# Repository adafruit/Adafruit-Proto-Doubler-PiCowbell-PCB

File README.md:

## Adafruit Proto Doubler PiCowbell for Pico and PicoW PCB

<a href="http://www.adafruit.com/products/5906"><br/>
Click here to purchase one from the Adafruit shop</a>

PCB files for the Adafruit Proto Doubler PiCowbell for Pico and PicoW. 

Format is EagleCAD schematic and board layout
* https://www.adafruit.com/product/5906

### Description

The Adafruit Proto Doubler PiCowBell is intended to be treated like a mini solder-less proto plate to simplify programming and sensor connectivity for your Raspberry Pi Pico board. Reset button? Yes! STEMMA QT / Qwiic connector for fast I2C? Indeed. Battery with recharging and on/off switch? Affirmative. Plug-and-play so no soldering necessary when used with a Pico H or Pico WH? Here you go!

The Doubler is like if we used a 'Clone Tool' on the Proto Under Plate PiCowbell - you get two slots side-by-side which means you can easily add accessories to your Pico or Pico W without soldering on any stacking headers.

### LiPoly Battery Charging Support
The Doubler also gives you Lipoly/LiIon support circuitry so you can take your Pico project on the go. Use any 3.7V/4.2V single-cell Lithium battery with a JST 2-PH connector in the correct polarity. The battery will automagically charge with the Pico is plugged into USB, and switch over seamlessly to battery when USB power is removed.

By default the charge rate is 500mA for use with 500mAh+ sized batteries. You can cut a jumper to reduce the charge rate to 250mA if using 250mAh to 500mAh battery. So you don't have to unplug the battery often, a slide switch is connected to the Pico Enable pin, so you can disable the Pico's 3.3V power supply completely - this is as close as we can get to 'turning off' the Pico.

### Alkaline/NiMH Battery Pack Support
You can also cut a different jumper to disconnect the charger completely from the battery, which means you can use 3xAA or 3xAAA battery packs for alkaline or NiMH battery usage. Of course, you will need an external NiMH charger in that case. 

### Double Socket Headers
This board has double sockets already soldered on, you can plug in your Pico and 'Bell boards directly in, and get access to a prototyping area underneath as well as a second row of socket pins. The second row means you can connect wires just by poking them into the header, either directly to LEDs or buttons or to jumper to a breadboard. So you don't have to look up or count pins, each socket is nicely labeled. There's also 4 mounting holes for easy attachment to an underplate. 

The dual socket headers we use are 'hollow' - that means you can connect through the back if desired. Specifically, you can use Pico Stacking Headers to plug through to some other device that is expecting Pico pins. Also, in theory, if you soldered pin headers on the 'wrong side' of a Pico, you could plug it up through the bottom.

We recommend picking up a set of little rubber feet to protect your desk if you're not mounting this board to something else.

### Features:
* Two 2x20 slim socket headers - plug in your Pico and desired 'Bell and have an extra row of sockets for each pin!
* JST PH connector for LiIon/LiPoly or Alkaline/NiMH battery usage - be sure to cut the "disable charge" jumper to use Alkaline/NiMH batteries.
* LiPoly/LiIon charging circuitry for any 3.7V/4.2V nominal 1-cell battery. Default rate is 500mA, can be set to 250mA by cutting the charge-rate jumper on bottom. Two indicator LEDs let you know if battery is charging (orange) or complete (green)
* Slide switch connected to the Pico Enable pin, which will disable the 3.3V power supply.
* Reset button that sticks out the end
* JST SH connector for I2C / Stemma QT / Qwiic connection. Or can use it for plain GPIO wiring if you don't have any I2C devices to attach. Provides 3V, GND, IO4 (SDA), and IO5 (SCL)
* There is an extra set of 4 breakout holes next to the JST SH if you want more I2C connections or want to re-assign the I2C port.
* 3 hole-connected strips are in the center areas. You can cut the traces between the holes, but they're intended to be treated like a mini-mini breadboard
* Nearly-every pad on the Pico has a duplicate hole pad next to it for solder-jumpering
* The ground pads have white silkscreen rectangles to easily identify, plus one long ground strip near the reset button
* One long strip of connected holes for 3.3V power
* Gold-plated pads for easy soldering

We do not have I2C pullups on the board, but your Qwiic/QT breakout board or accessory likely already has them onboard. If using the Philhower Arduino core, the Wire peripheral is already set up to use IO4 and IO5. If using CircuitPython or MicroPython, you'll need to let the code know to look at 4+5 for SDA+SCL pins.

### License

Adafruit invests time and resources providing this open source design, please support Adafruit and open-source hardware by purchasing products from [Adafruit](https://www.adafruit.com)!

Designed by Limor Fried/Ladyada for Adafruit Industries.

Creative Commons Attribution/Share-Alike, all text above must be included in any redistribution. 
See license.txt for additional details.

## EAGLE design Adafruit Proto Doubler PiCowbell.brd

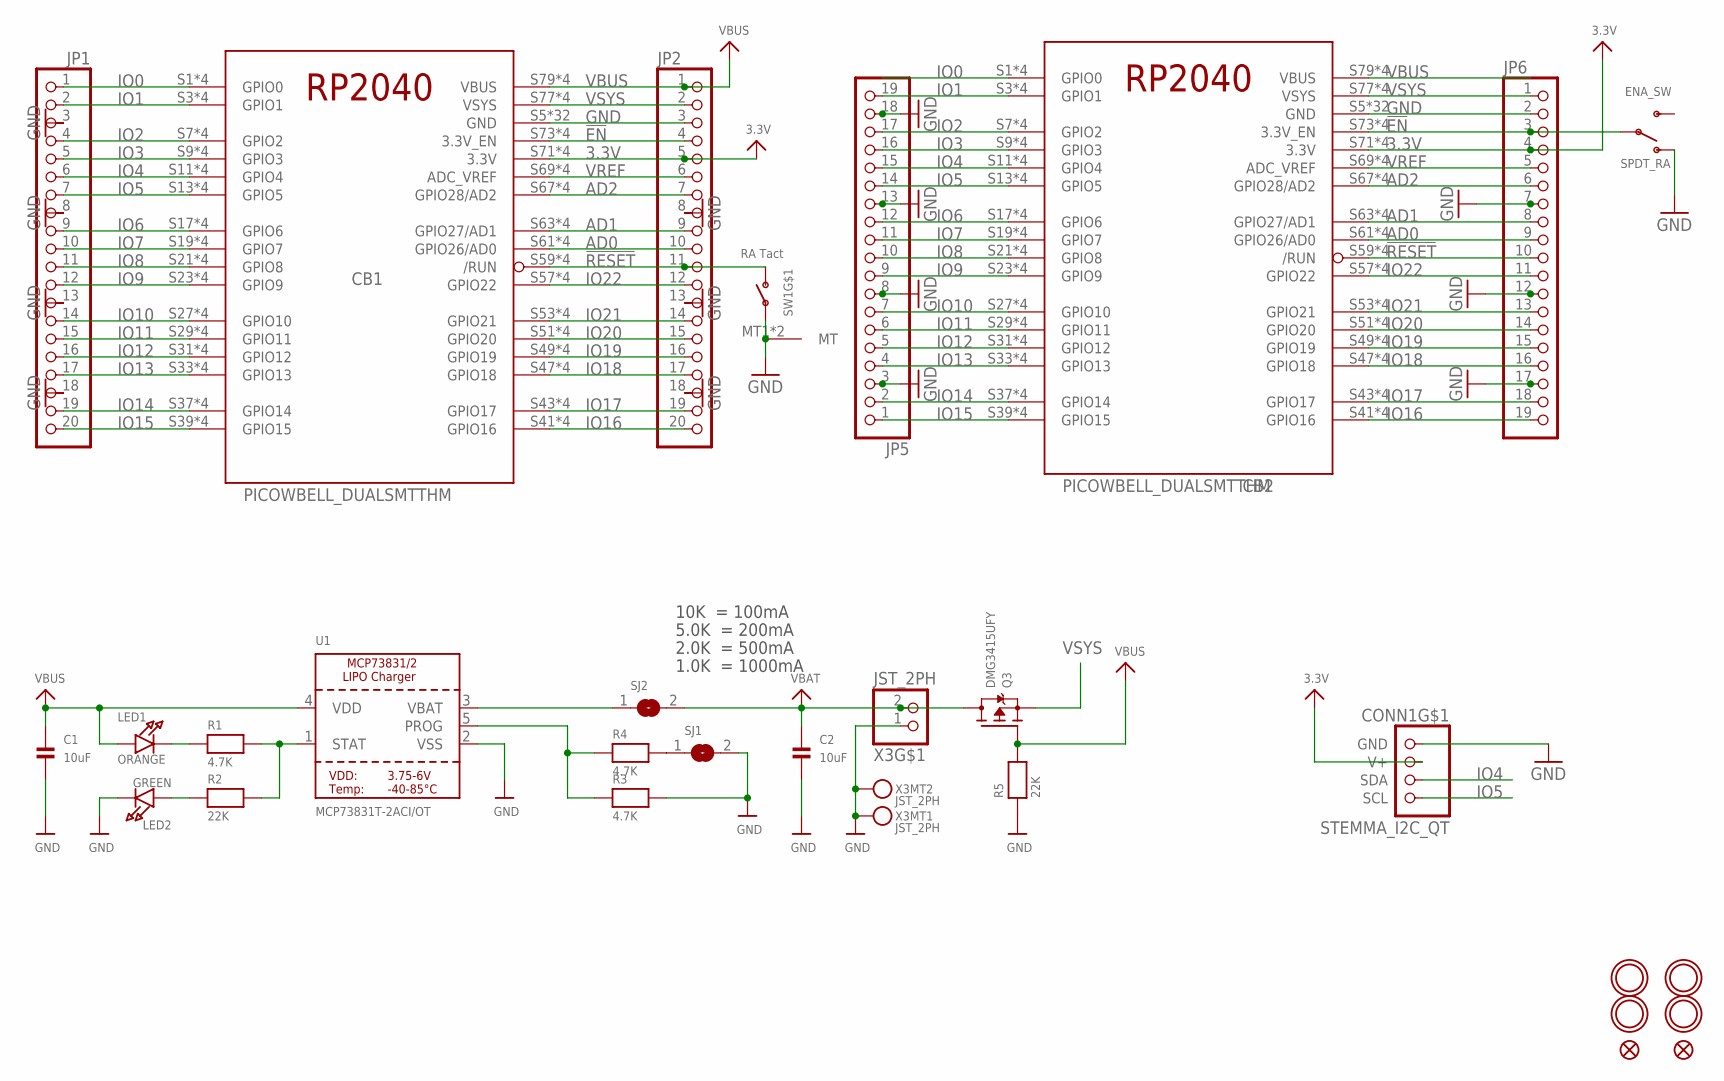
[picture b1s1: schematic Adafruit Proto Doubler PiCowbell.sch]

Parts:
C1, C2: 10uF; 0805-NO
CB1, CB2: PICOWBELL_DUALSMTTHM
CONN1: STEMMA_I2C_QT; JST_SH4
ENA_SW: SPDT_RA; SPDT_SMT_SSSS811101
FID1, FID2: FIDUCIAL_1MM
JP1, JP2: HEADER-1X20_70MIL; 1X20_ROUND_70MIL
JP5, JP6: HEADER-1X19; 1X19_ROUND
LED1: ORANGE; CHIPLED_0603_NOOUTLINE
LED2: GREEN; CHIPLED_0603_NOOUTLINE
Q3: DMG3415UFY; DFN2015-3
R1, R3, R4: 4.7K; _0402NO
R2, R5: 22K; _0402NO
SJ1, SJ2: SOLDERJUMPERCLOSED; SOLDERJUMPER_CLOSEDWIRE
SW1: RA Tact; SPST_TACTILE_RA
U1: MCP73831T-2ACI/OT; SOT23-5; JLC_ROTATION 0
U$5, U$7, U$15, U$16: MOUNTINGHOLE2.5; MOUNTINGHOLE_2.5_PLATED
X3: JST_2PH; JSTPH2_BATT

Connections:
3.3V: CB1.S71 (3.3V), CB1.S72 (3.3V), CB1.T71 (3.3V), CB1.T72 (3.3V), CB2.S71 (3.3V), CB2.S72 (3.3V), CB2.T71 (3.3V), CB2.T72 (3.3V), CONN1.2 (V+), JP2.5, JP6.4
!EN: CB1.S73 (3.3V_EN), CB1.S74 (3.3V_EN), CB1.T73 (3.3V_EN), CB1.T74 (3.3V_EN), CB2.S73 (3.3V_EN), CB2.S74 (3.3V_EN), CB2.T73 (3.3V_EN), CB2.T74 (3.3V_EN), ENA_SW.B, JP2.4, JP6.3
!RESET: CB1.S59 (/RUN), CB1.S60 (/RUN), CB1.T59 (/RUN), CB1.T60 (/RUN), CB2.S59 (/RUN), CB2.S60 (/RUN), CB2.T59 (/RUN), CB2.T60 (/RUN), JP2.11, JP6.10, SW1.2 (S)
AD0: CB1.S61 (GPIO26/AD0), CB1.S62 (GPIO26/AD0), CB1.T61 (GPIO26/AD0), CB1.T62 (GPIO26/AD0), CB2.S61 (GPIO26/AD0), CB2.S62 (GPIO26/AD0), CB2.T61 (GPIO26/AD0), CB2.T62 (GPIO26/AD0), JP2.10, JP6.9
AD1: CB1.S63 (GPIO27/AD1), CB1.S64 (GPIO27/AD1), CB1.T63 (GPIO27/AD1), CB1.T64 (GPIO27/AD1), CB2.S63 (GPIO27/AD1), CB2.S64 (GPIO27/AD1), CB2.T63 (GPIO27/AD1), CB2.T64 (GPIO27/AD1), JP2.9, JP6.8
AD2: CB1.S67 (GPIO28/AD2), CB1.S68 (GPIO28/AD2), CB1.T67 (GPIO28/AD2), CB1.T68 (GPIO28/AD2), CB2.S67 (GPIO28/AD2), CB2.S68 (GPIO28/AD2), CB2.T67 (GPIO28/AD2), CB2.T68 (GPIO28/AD2), JP2.7, JP6.6
GND: C1.2, C2.2, CB1.S5 (GND), CB1.S6 (GND), CB1.S15 (GND), CB1.S16 (GND), CB1.S25 (GND), CB1.S26 (GND), CB1.S35 (GND), CB1.S36 (GND), CB1.S45 (GND), CB1.S46 (GND), CB1.S55 (GND), CB1.S56 (GND), CB1.S65 (GND), CB1.S66 (GND), CB1.S75 (GND), CB1.S76 (GND), CB1.T5 (GND), CB1.T6 (GND), CB1.T15 (GND), CB1.T16 (GND), CB1.T25 (GND), CB1.T26 (GND), CB1.T35 (GND), CB1.T36 (GND), CB1.T45 (GND), CB1.T46 (GND), CB1.T55 (GND), CB1.T56 (GND), CB1.T65 (GND), CB1.T66 (GND), CB1.T75 (GND), CB1.T76 (GND), CB2.S5 (GND), CB2.S6 (GND), CB2.S15 (GND), CB2.S16 (GND), CB2.S25 (GND), CB2.S26 (GND), CB2.S35 (GND), CB2.S36 (GND), CB2.S45 (GND), CB2.S46 (GND), CB2.S55 (GND), CB2.S56 (GND), CB2.S65 (GND), CB2.S66 (GND), CB2.S75 (GND), CB2.S76 (GND), CB2.T5 (GND), CB2.T6 (GND), CB2.T15 (GND), CB2.T16 (GND), CB2.T25 (GND), CB2.T26 (GND), CB2.T35 (GND), CB2.T36 (GND), CB2.T45 (GND), CB2.T46 (GND), CB2.T55 (GND), CB2.T56 (GND), CB2.T65 (GND), CB2.T66 (GND), CB2.T75 (GND), CB2.T76 (GND), CONN1.1 (GND), ENA_SW.A (O), JP1.3, JP1.8, JP1.13, JP1.18, JP2.3, JP2.8, JP2.13, JP2.18, JP5.3, JP5.8, JP5.13, JP5.18, JP6.2, JP6.7, JP6.12, JP6.17, LED2.C, R3.2, R5.1, SJ1.2, SW1.1, SW1.MT1 (MT), SW1.MT2 (MT), U1.2 (VSS), X3.1, X3.NC1, X3.NC2
IO0: CB1.S1 (GPIO0), CB1.S2 (GPIO0), CB1.T1 (GPIO0), CB1.T2 (GPIO0), CB2.S1 (GPIO0), CB2.S2 (GPIO0), CB2.T1 (GPIO0), CB2.T2 (GPIO0), JP1.1
IO1: CB1.S3 (GPIO1), CB1.S4 (GPIO1), CB1.T3 (GPIO1), CB1.T4 (GPIO1), CB2.S3 (GPIO1), CB2.S4 (GPIO1), CB2.T3 (GPIO1), CB2.T4 (GPIO1), JP1.2, JP5.19
IO2: CB1.S7 (GPIO2), CB1.S8 (GPIO2), CB1.T7 (GPIO2), CB1.T8 (GPIO2), CB2.S7 (GPIO2), CB2.S8 (GPIO2), CB2.T7 (GPIO2), CB2.T8 (GPIO2), JP1.4, JP5.17
IO3: CB1.S9 (GPIO3), CB1.S10 (GPIO3), CB1.T9 (GPIO3), CB1.T10 (GPIO3), CB2.S9 (GPIO3), CB2.S10 (GPIO3), CB2.T9 (GPIO3), CB2.T10 (GPIO3), JP1.5, JP5.16
IO4: CB1.S11 (GPIO4), CB1.S12 (GPIO4), CB1.T11 (GPIO4), CB1.T12 (GPIO4), CB2.S11 (GPIO4), CB2.S12 (GPIO4), CB2.T11 (GPIO4), CB2.T12 (GPIO4), CONN1.3 (SDA), JP1.6, JP5.15
IO5: CB1.S13 (GPIO5), CB1.S14 (GPIO5), CB1.T13 (GPIO5), CB1.T14 (GPIO5), CB2.S13 (GPIO5), CB2.S14 (GPIO5), CB2.T13 (GPIO5), CB2.T14 (GPIO5), CONN1.4 (SCL), JP1.7, JP5.14
IO6: CB1.S17 (GPIO6), CB1.S18 (GPIO6), CB1.T17 (GPIO6), CB1.T18 (GPIO6), CB2.S17 (GPIO6), CB2.S18 (GPIO6), CB2.T17 (GPIO6), CB2.T18 (GPIO6), JP1.9, JP5.12
IO7: CB1.S19 (GPIO7), CB1.S20 (GPIO7), CB1.T19 (GPIO7), CB1.T20 (GPIO7), CB2.S19 (GPIO7), CB2.S20 (GPIO7), CB2.T19 (GPIO7), CB2.T20 (GPIO7), JP1.10, JP5.11
IO8: CB1.S21 (GPIO8), CB1.S22 (GPIO8), CB1.T21 (GPIO8), CB1.T22 (GPIO8), CB2.S21 (GPIO8), CB2.S22 (GPIO8), CB2.T21 (GPIO8), CB2.T22 (GPIO8), JP1.11, JP5.10
IO9: CB1.S23 (GPIO9), CB1.S24 (GPIO9), CB1.T23 (GPIO9), CB1.T24 (GPIO9), CB2.S23 (GPIO9), CB2.S24 (GPIO9), CB2.T23 (GPIO9), CB2.T24 (GPIO9), JP1.12, JP5.9
IO10: CB1.S27 (GPIO10), CB1.S28 (GPIO10), CB1.T27 (GPIO10), CB1.T28 (GPIO10), CB2.S27 (GPIO10), CB2.S28 (GPIO10), CB2.T27 (GPIO10), CB2.T28 (GPIO10), JP1.14, JP5.7
IO11: CB1.S29 (GPIO11), CB1.S30 (GPIO11), CB1.T29 (GPIO11), CB1.T30 (GPIO11), CB2.S29 (GPIO11), CB2.S30 (GPIO11), CB2.T29 (GPIO11), CB2.T30 (GPIO11), JP1.15, JP5.6
IO12: CB1.S31 (GPIO12), CB1.S32 (GPIO12), CB1.T31 (GPIO12), CB1.T32 (GPIO12), CB2.S31 (GPIO12), CB2.S32 (GPIO12), CB2.T31 (GPIO12), CB2.T32 (GPIO12), JP1.16, JP5.5
IO13: CB1.S33 (GPIO13), CB1.S34 (GPIO13), CB1.T33 (GPIO13), CB1.T34 (GPIO13), CB2.S33 (GPIO13), CB2.S34 (GPIO13), CB2.T33 (GPIO13), CB2.T34 (GPIO13), JP1.17, JP5.4
IO14: CB1.S37 (GPIO14), CB1.S38 (GPIO14), CB1.T37 (GPIO14), CB1.T38 (GPIO14), CB2.S37 (GPIO14), CB2.S38 (GPIO14), CB2.T37 (GPIO14), CB2.T38 (GPIO14), JP1.19, JP5.2
IO15: CB1.S39 (GPIO15), CB1.S40 (GPIO15), CB1.T39 (GPIO15), CB1.T40 (GPIO15), CB2.S39 (GPIO15), CB2.S40 (GPIO15), CB2.T39 (GPIO15), CB2.T40 (GPIO15), JP1.20, JP5.1
IO16: CB1.S41 (GPIO16), CB1.S42 (GPIO16), CB1.T41 (GPIO16), CB1.T42 (GPIO16), CB2.S41 (GPIO16), CB2.S42 (GPIO16), CB2.T41 (GPIO16), CB2.T42 (GPIO16), JP2.20, JP6.19
IO17: CB1.S43 (GPIO17), CB1.S44 (GPIO17), CB1.T43 (GPIO17), CB1.T44 (GPIO17), CB2.S43 (GPIO17), CB2.S44 (GPIO17), CB2.T43 (GPIO17), CB2.T44 (GPIO17), JP2.19, JP6.18
IO18: CB1.S47 (GPIO18), CB1.S48 (GPIO18), CB1.T47 (GPIO18), CB1.T48 (GPIO18), CB2.S47 (GPIO18), CB2.S48 (GPIO18), CB2.T47 (GPIO18), CB2.T48 (GPIO18), JP2.17, JP6.16
IO19: CB1.S49 (GPIO19), CB1.S50 (GPIO19), CB1.T49 (GPIO19), CB1.T50 (GPIO19), CB2.S49 (GPIO19), CB2.S50 (GPIO19), CB2.T49 (GPIO19), CB2.T50 (GPIO19), JP2.16, JP6.15
IO20: CB1.S51 (GPIO20), CB1.S52 (GPIO20), CB1.T51 (GPIO20), CB1.T52 (GPIO20), CB2.S51 (GPIO20), CB2.S52 (GPIO20), CB2.T51 (GPIO20), CB2.T52 (GPIO20), JP2.15, JP6.14
IO21: CB1.S53 (GPIO21), CB1.S54 (GPIO21), CB1.T53 (GPIO21), CB1.T54 (GPIO21), CB2.S53 (GPIO21), CB2.S54 (GPIO21), CB2.T53 (GPIO21), CB2.T54 (GPIO21), JP2.14, JP6.13
IO22: CB1.S57 (GPIO22), CB1.S58 (GPIO22), CB1.T57 (GPIO22), CB1.T58 (GPIO22), CB2.S57 (GPIO22), CB2.S58 (GPIO22), CB2.T57 (GPIO22), CB2.T58 (GPIO22), JP2.12, JP6.11
unnamed: R4.2, SJ1.1
unnamed: SJ2.1, U1.3 (VBAT)
unnamed: LED1.C, R1.1
unnamed: R1.2, R2.2, U1.1 (STAT)
unnamed: LED2.A, R2.1
unnamed: R3.1, R4.1, U1.5 (PROG)
VBAT: C2.1, Q3.3 (D), SJ2.2, X3.2
VBUS: C1.1, CB1.S79 (VBUS), CB1.S80 (VBUS), CB1.T79 (VBUS), CB1.T80 (VBUS), CB2.S79 (VBUS), CB2.S80 (VBUS), CB2.T79 (VBUS), CB2.T80 (VBUS), JP2.1, LED1.A, Q3.1 (G), R5.2, U1.4 (VDD)
VREF: CB1.S69 (ADC_VREF), CB1.S70 (ADC_VREF), CB1.T69 (ADC_VREF), CB1.T70 (ADC_VREF), CB2.S69 (ADC_VREF), CB2.S70 (ADC_VREF), CB2.T69 (ADC_VREF), CB2.T70 (ADC_VREF), JP2.6, JP6.5
VSYS: CB1.S77 (VSYS), CB1.S78 (VSYS), CB1.T77 (VSYS), CB1.T78 (VSYS), CB2.S77 (VSYS), CB2.S78 (VSYS), CB2.T77 (VSYS), CB2.T78 (VSYS), JP2.2, JP6.1, Q3.2 (S)

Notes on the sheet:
10K = 100mA
5.0K = 200mA
2.0K = 500mA
1.0K = 1000mA

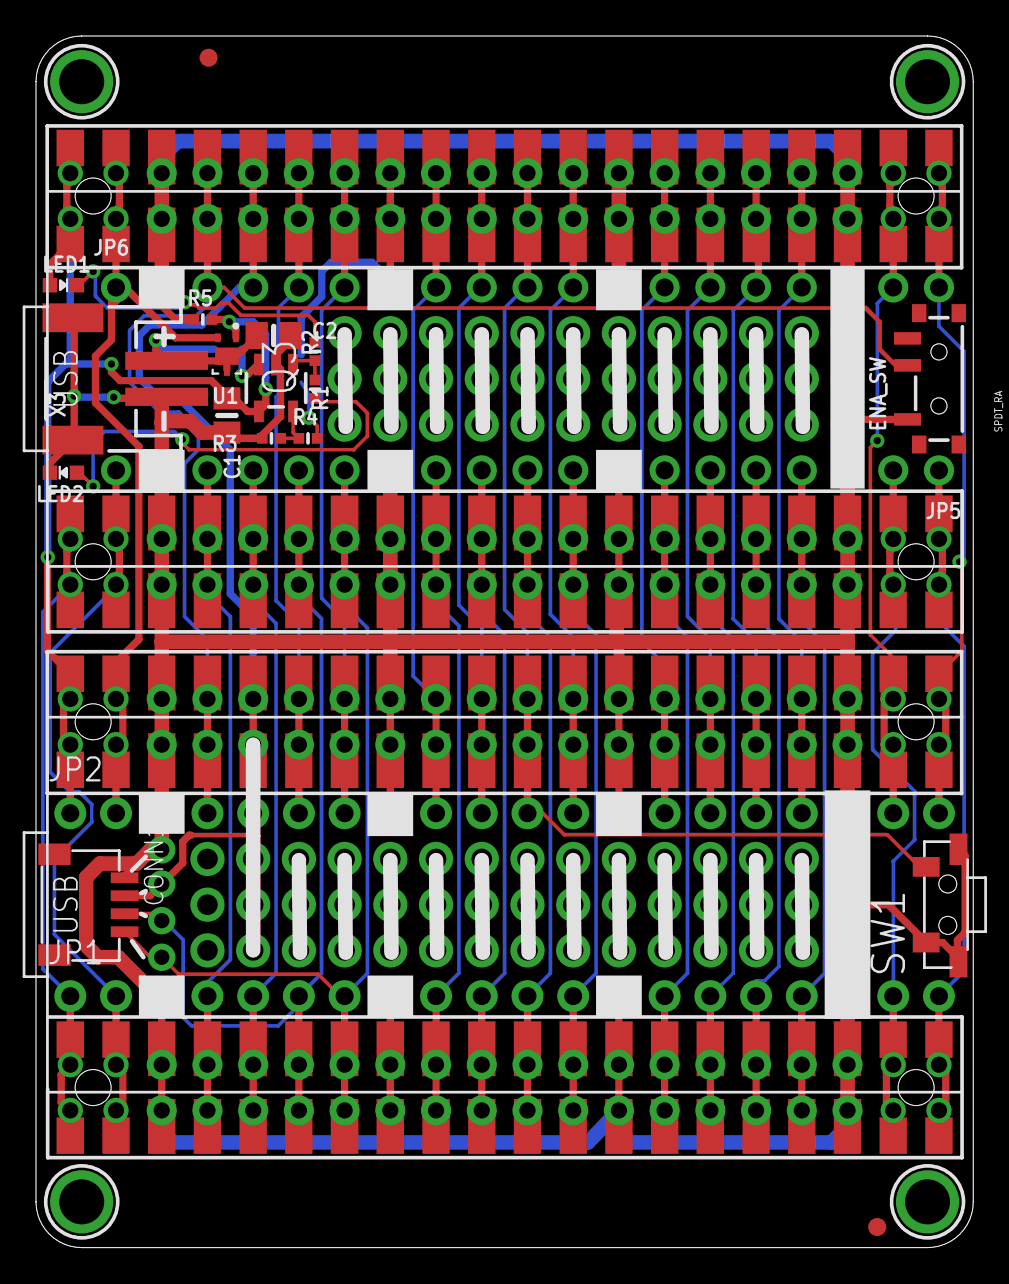
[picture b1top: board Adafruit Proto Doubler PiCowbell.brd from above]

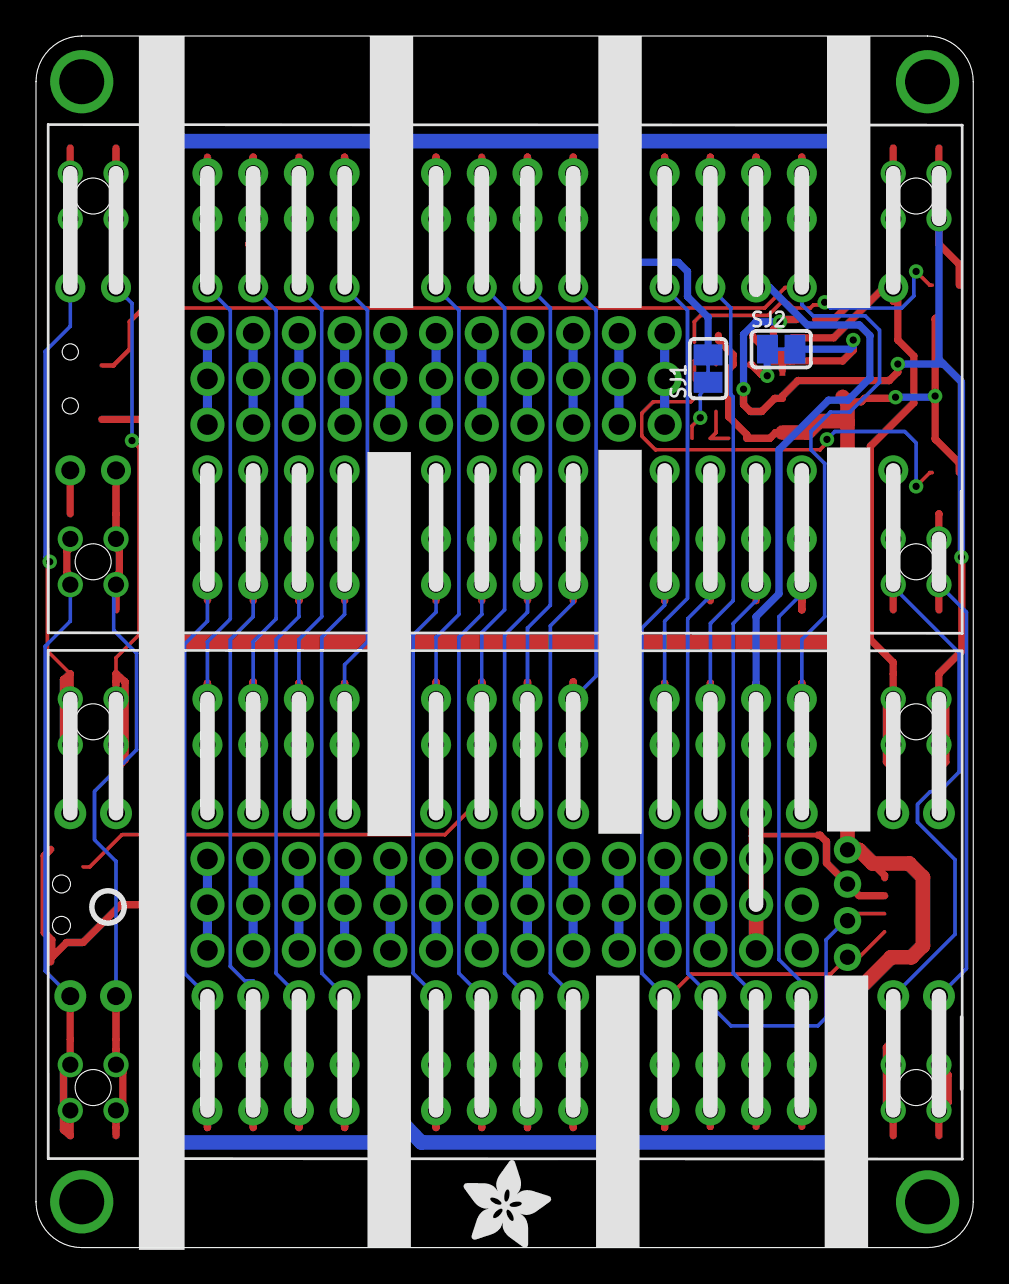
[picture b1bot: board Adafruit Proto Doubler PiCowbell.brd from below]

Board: 2 copper layers, 52.1 x 67.3 mm, 80 parts (17 on the bottom side), 40 nets.

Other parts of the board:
PLABEL0: PLABEL0
PLABEL1: PLABEL1
PLABEL2: PLABEL2
PLABEL3: PLABEL3
PLABEL4: PLABEL4
PLABEL5: PLABEL5
PLABEL6: PLABEL6
PLABEL7: PLABEL7
PLABEL8: PLABEL8
PLABEL9: PLABEL9
PLABEL10: PLABEL10
PLABEL11: PLABEL11
PLABEL12: PLABEL12
PLABEL13: PLABEL13
PLABEL14: PLABEL14
PLABEL15: PLABEL15
PLABEL16: PLABEL16
PLABEL36: PLABEL36
PLABEL37: PLABEL37
PLABEL38: PLABEL38
PLABEL39: PLABEL39
PLABEL40: PLABEL40
PLABEL41: PLABEL41
PLABEL42: PLABEL42
PLABEL43: PLABEL43
PLABEL44: PLABEL44
PLABEL45: PLABEL45
PLABEL46: PLABEL46
PLABEL47: PLABEL47
PLABEL48: PLABEL48
PLABEL59: PLABEL17
PLABEL60: PLABEL18
PLABEL61: PLABEL19
PLABEL62: PLABEL20
PLABEL63: PLABEL21
PLABEL64: PLABEL22
PLABEL65: PLABEL23
PLABEL66: PLABEL24
PLABEL67: PLABEL25
PLABEL68: PLABEL26
PLABEL69: PLABEL27
PLABEL70: PLABEL28
PLABEL71: PLABEL29
PLABEL72: PLABEL30
PLABEL73: PLABEL31
PLABEL74: PLABEL32
PLABEL75: PLABEL33
PLABEL76: PLABEL34
PLABEL77: PLABEL35
U$6: PCBFEAT-REV-040
U$10: ADAFRUIT_5MM

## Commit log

2024-03-14 cookiecutter

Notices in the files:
parts and their libraries:
microbuilder: This work is placed in the public domain, and may be freely used for commercial and non-commercial work with the following conditions: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
